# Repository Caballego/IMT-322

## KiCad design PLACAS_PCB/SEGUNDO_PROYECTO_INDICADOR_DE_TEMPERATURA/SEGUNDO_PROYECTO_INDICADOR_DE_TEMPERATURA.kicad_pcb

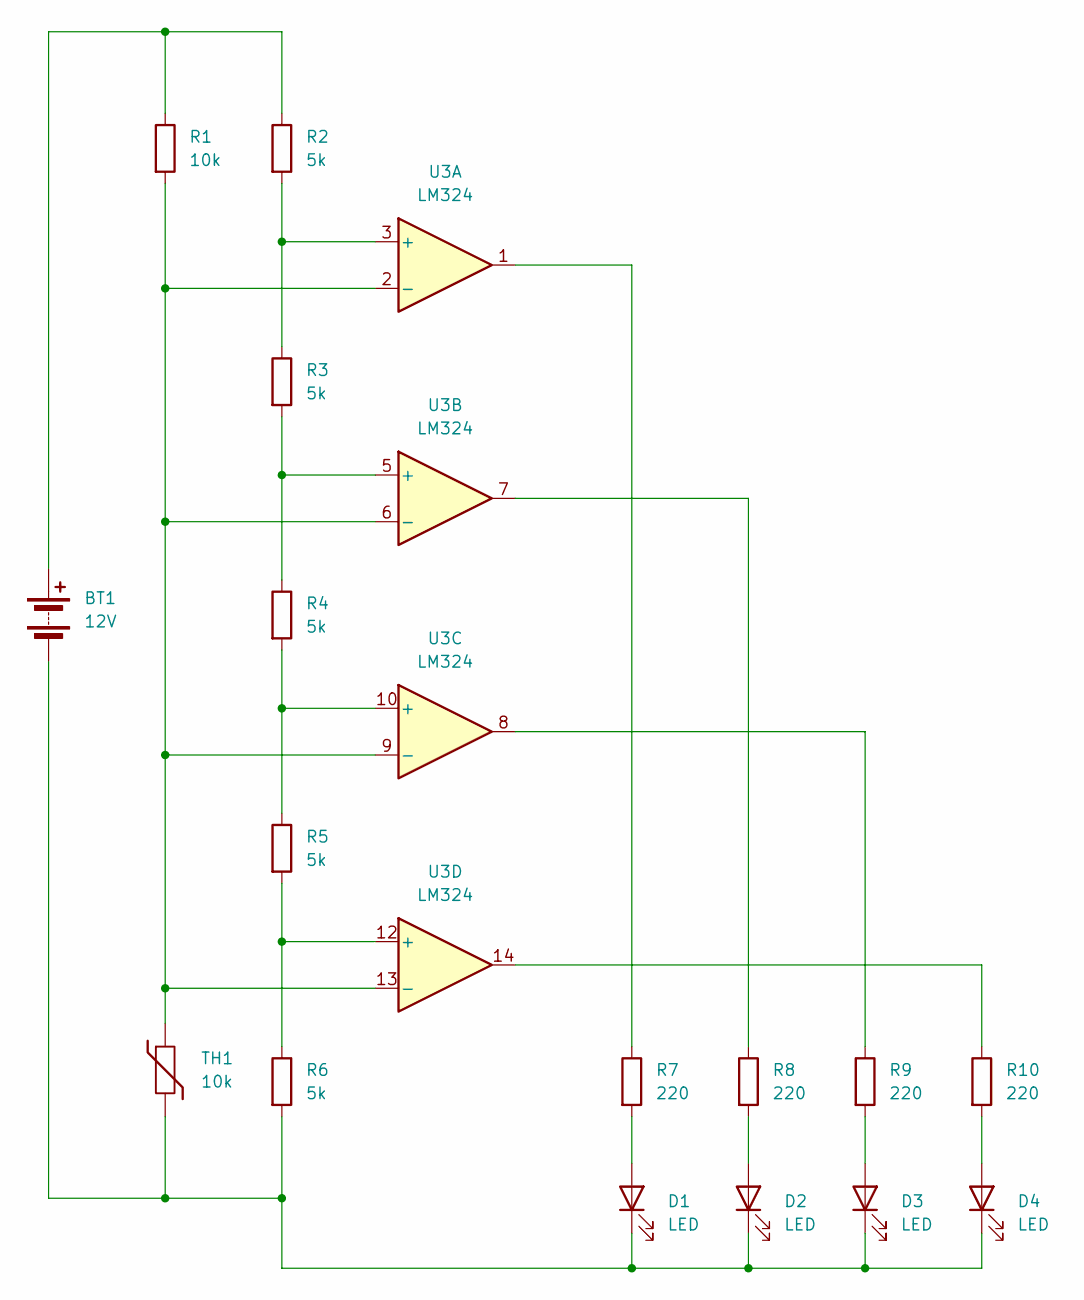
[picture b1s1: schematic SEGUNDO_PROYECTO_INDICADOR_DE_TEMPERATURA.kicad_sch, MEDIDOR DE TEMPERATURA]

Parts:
BT1: 12V; TerminalBlock_Phoenix_MKDS-1,5-2-5.08_1x02_P5.08mm_Horizont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
D1, D2, D3, D4: LED; LED_D3.0mm
R1: 10k; R_0201_0603Metric
R2, R3, R4, R5, R6: 5k; R_0201_0603Metric
R7, R8, R9, R10: 220; R_0201_0603Metric
TH1: 10k; R_0201_0603Metric
U3: LM324; DIP-14_W7.62mm

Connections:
unnamed: BT1.1 (+), R1.1, R2.1
unnamed: BT1.2 (-), D1.1 (K), D2.1 (K), D3.1 (K), D4.1 (K), R6.2, TH1.2
unnamed: D1.2 (A), R7.2
unnamed: D2.2 (A), R8.2
unnamed: D3.2 (A), R9.2
unnamed: D4.2 (A), R10.2
unnamed: R7.1, U3.1
unnamed: R8.1, U3.7
unnamed: R9.1, U3.8
unnamed: R10.1, U3.14
unnamed: R2.2, R3.1, U3.3 (+)
unnamed: R1.2, TH1.1, U3.2 (-), U3.6 (-), U3.9 (-), U3.13 (-)
unnamed: R3.2, R4.1, U3.5 (+)
unnamed: R4.2, R5.1, U3.10 (+)
unnamed: R5.2, R6.1, U3.12 (+)

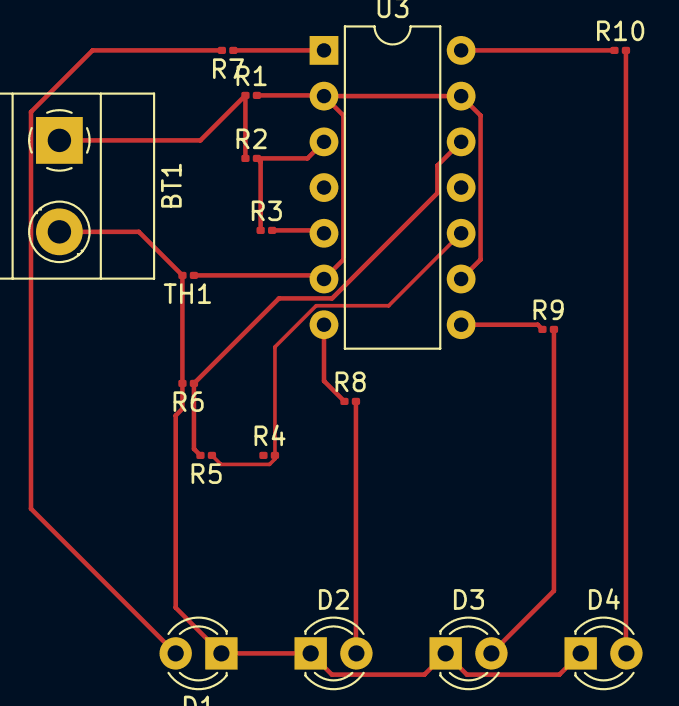
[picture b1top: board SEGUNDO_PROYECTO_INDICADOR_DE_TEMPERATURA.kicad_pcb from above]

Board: 2 copper layers, 17 parts (0 on the bottom side), 15 nets.

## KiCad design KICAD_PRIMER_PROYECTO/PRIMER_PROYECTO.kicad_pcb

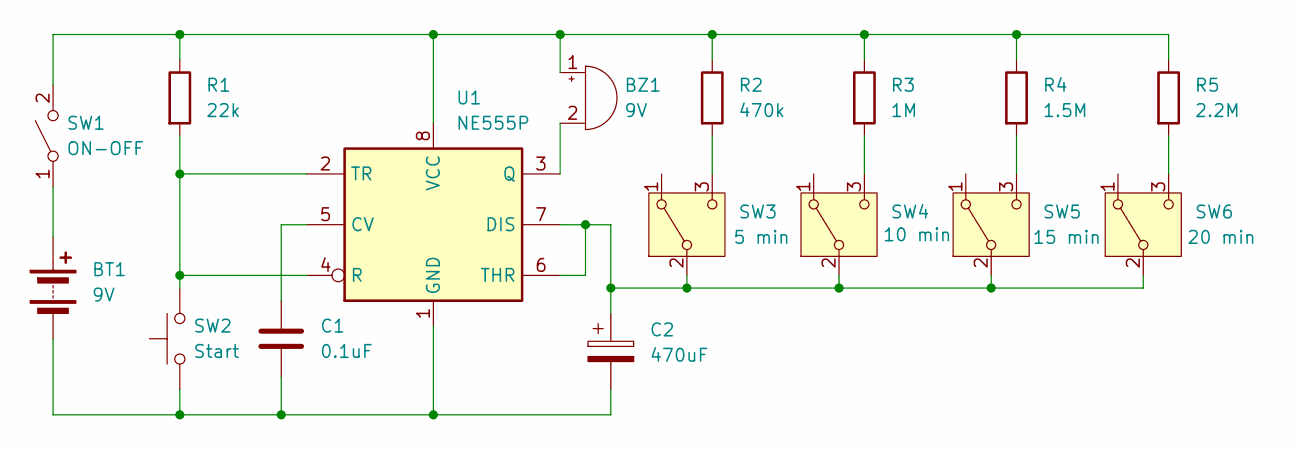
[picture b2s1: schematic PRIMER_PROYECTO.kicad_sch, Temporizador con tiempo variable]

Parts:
BT1: 9V; TerminalBlock_Phoenix_MKDS-1,5-2-5.08_1x02_P5.08mm_Horizont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
BZ1: 9V; Buzzer_12x9.5RM7.6
C1: 0.1uF; C_0201_0603Metric
C2: 470uF; CP_Elec_3x5.3
R1: 22k; R_1206_3216Metric
R2: 470k; R_1206_3216Metric
R3: 1M; R_1206_3216Metric
R4: 1.5M; R_1206_3216Metric
R5: 2.2M; R_1206_3216Metric
SW1: ON-OFF; SW_Push_1TS009xxxx-xxxx-xxxx_6x6x5mm
SW2: Start; SW_DIP_SPSTx01_Slide_6.7x4.1mm_W6.73mm_P2.54mm_LowProfile_J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
SW3: 5 min; SW_Slide_SPDT_Straight_CK_OS102011MS2Q
SW4: 10 min; SW_Slide_SPDT_Straight_CK_OS102011MS2Q
SW5: 15 min; SW_Slide_SPDT_Straight_CK_OS102011MS2Q
SW6: 20 min; SW_Slide_SPDT_Straight_CK_OS102011MS2Q
U1: NE555P; DIP-8_W7.62mm

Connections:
unnamed: BT1.1 (+), SW1.1 (A)
unnamed: BT1.2 (-), C1.2, C2.2, SW2.1, U1.1 (GND)
unnamed: BZ1.1 (+), R1.1, R2.1, R3.1, R4.1, R5.1, SW1.2 (B), U1.8 (VCC)
unnamed: BZ1.2 (-), U1.3 (Q)
unnamed: C2.1, SW3.2 (B), SW4.2 (B), SW5.2 (B), SW6.2 (B), U1.6 (THR), U1.7 (DIS)
unnamed: R2.2, SW3.3 (C)
unnamed: R3.2, SW4.3 (C)
unnamed: R4.2, SW5.3 (C)
unnamed: R5.2, SW6.3 (C)
unnamed: C1.1, U1.5 (CV)
unnamed: R1.2, SW2.2, U1.2 (TR), U1.4 (R)

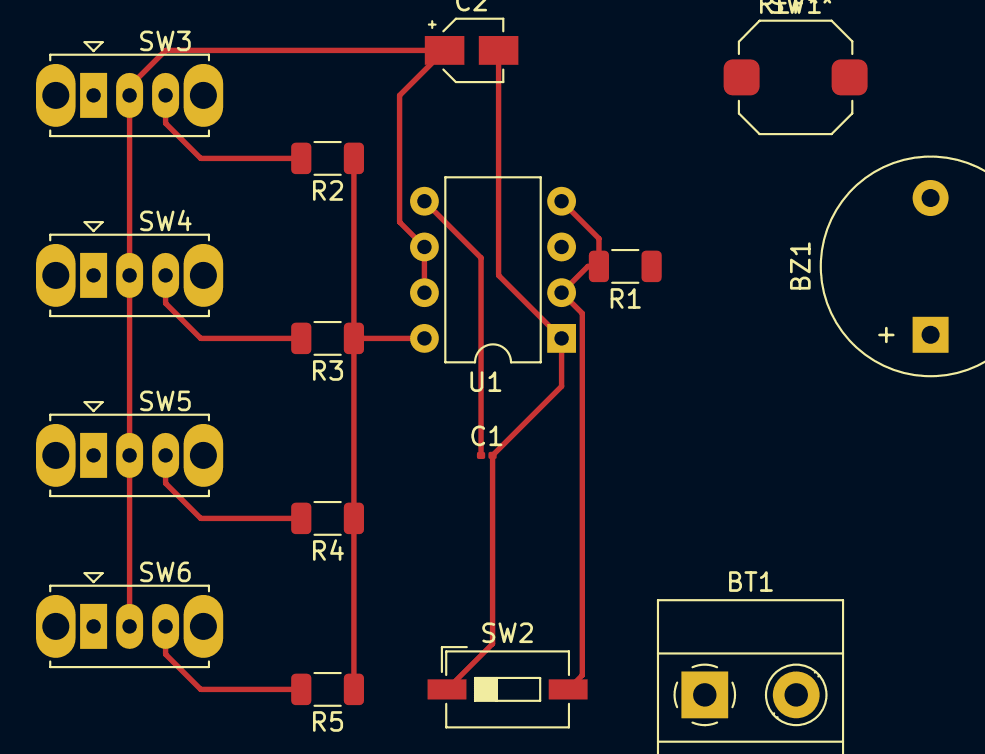
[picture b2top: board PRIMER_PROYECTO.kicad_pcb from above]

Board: 2 copper layers, 16 parts (0 on the bottom side), 11 nets.

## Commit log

2024-02-17 Actualizando Readme
2024-02-17 Happens
2024-02-17 Eliminando txt
2024-03-08 Práctica 1-Parte 1
2024-03-09 Práctica 1-Parte 2
2024-03-09 Práctica 2-Parte 1
2024-03-09 Práctica 2-Parte 2
2024-03-09 Práctica 3-Parte 1
2024-03-09 Práctica 3-Parte 2
2024-03-19 EXAMEN DE LABORATORIO N1
2024-03-19 EXAMEN DE LABORATORIO 1
2024-04-12 Eliminando carpeta
2024-04-12 Práctica 4
2024-04-12 Placa PCB
2024-04-13 Actualización PCB Kicad
2024-04-13 Avance KICAD PCB
2024-04-14 Actualizacion KICAD PCB
2024-04-20 Carga de práctica SEMAFORO
2024-04-20 Carga de práctica SENSOR_ULTRASONICO
2024-04-21 Actualización de prácticas en clase
2024-04-21 Creación carpeta PLACAS_PCB
2024-04-22 Carga de segunda Placa PCB
2024-04-22 Actualizacion Placa PCB Med. Temp.
2024-04-23 Carga de praćtica ASCENSOR
2024-05-21 PRACTICA BLINK EN RASPBERRY
2024-05-22 Carga de evaluación segundo parcial
2024-05-23 Carga de código examen recuperatorio
2024-05-23 Carga de diagrama FSM
2024-05-28 Carga de examen de laboratorio 3
2024-05-28 Carga de código de Raspberry
